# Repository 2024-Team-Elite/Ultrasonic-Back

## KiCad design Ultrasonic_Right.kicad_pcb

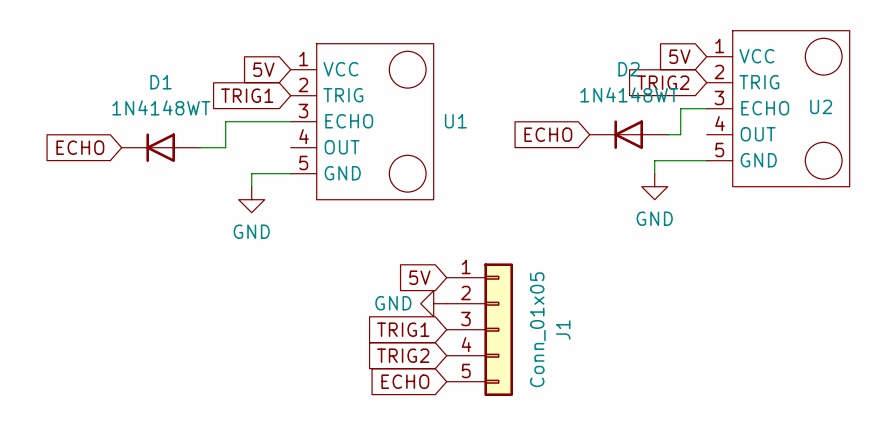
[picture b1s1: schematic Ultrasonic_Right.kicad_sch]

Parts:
D1, D2: 1N4148WT; D_SOD-123
J1: Conn_01x05; JST_XH_B5B-XH-A_1x05_P2.50mm_Vertical
U1, U2: PinHeader_1x05_P2.54mm_Vertical

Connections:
5V: J1.1, U1.1 (VCC), U2.1 (VCC)
ECHO: D1.1 (K), D2.1 (K), J1.5
GND: J1.2, U1.5 (GND), U2.5 (GND)
unnamed: D1.2 (A), U1.3 (ECHO)
unnamed: D2.2 (A), U2.3 (ECHO)
TRIG1: J1.3, U1.2 (TRIG)
TRIG2: J1.4, U2.2 (TRIG)

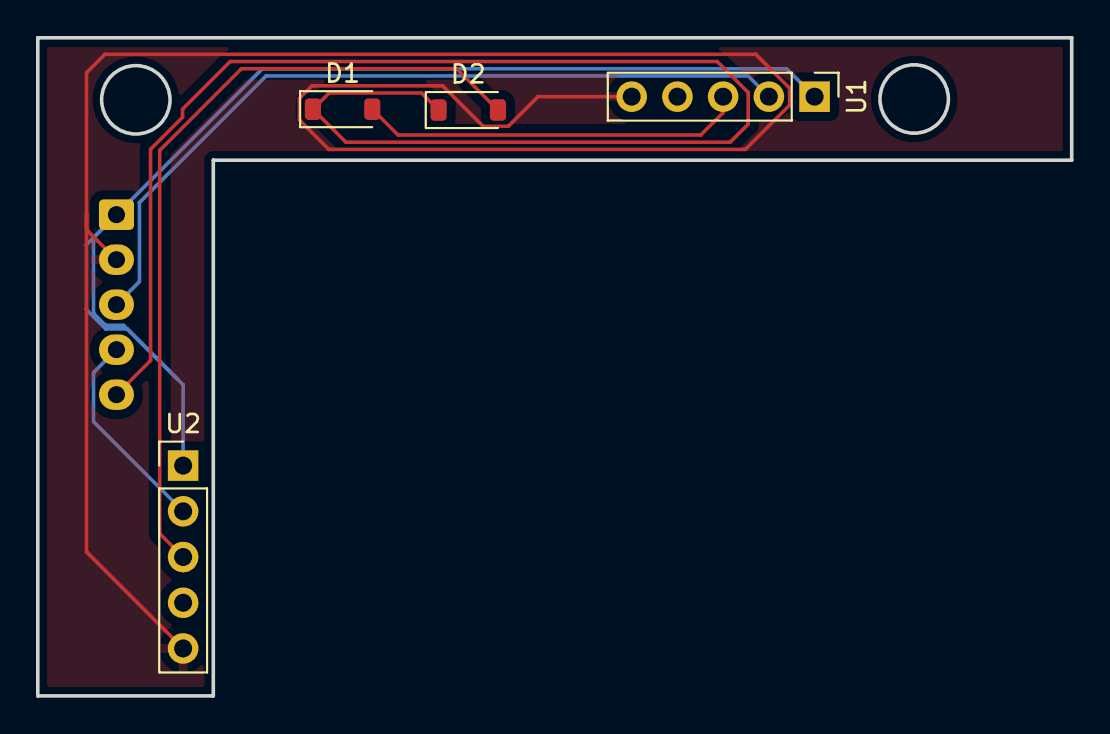
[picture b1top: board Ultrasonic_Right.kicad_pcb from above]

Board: 2 copper layers, 57.4 x 36.6 mm, 5 parts (1 on the bottom side), 7 nets.

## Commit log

2024-06-16 Finished
